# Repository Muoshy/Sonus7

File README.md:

# Sonus7
  Sonus7 is an analog seven-band spectrum bargraph with op amps. It consists of seven VU-meters, each being fed with a bandpass filter and peak detector circuit. 
  
  Each band has a spacing of 1.25 octaves. The bands are: 63 Hz, 160 Hz, 400 Hz, 1.25 kHz, 2.5 kHz, 6.25 kHz, 16 kHz. 
  
  The filters are second-order Multiple Feedback bandpass filters using TLC272 opamps. The VU-meters consist of a logaritmic comparator array, also using TLC272 opamps. The project is inspired by a reel of 2000 TLC272 bought cheaply at an auction.
  
# Features
- Fully analog (Except input stage)
- Seven frequency bands
- 10 levels per band
- 1.25 octave spacing
- 63 Hz to 16 kHz frequency range

# Filters
The filters were chosen to be Multiple Feedback filters since they allow independent adjustment of the gain $A_m$, filter quality $Q$ and mid frequency $f_m$. The transfer function and equations for calculating component values are taken from TI's design reference SLOD006B (16-31).

The gain and filter quality were set to $A_m = -10, \: Q = 6$ while capacitor values were chosen in the range of 33 to 0.33 nF to end up with reasonable resistor values. A MATLAB script is provided to calculate the exact resistor values and then round to nearest corresponding value from the E-24 series. The frequency responses are then simulated for the exact and rounded resistor values.

A final calculation is done to ensure the filter gains do not exceed the unity gain bandwidth (GBW) of the op amps. The actual amplification from the op amps is obtained from the noise gain. The noise gain is then multiplied with the corresponding mid frequency of each filter to obtain the (highest) GBW. This is also provided in the same MATLAB script. The calculation shows that all filters have a GBW below 2 MHz (TLC272), although the 16 kHz filter is close at 1.1 MHz. Thus, variations in temperature or other factors might limit the gain for 16 kHz filter and cause distortions.

The filtered signals are fed into peak detectors to obtain the audio level for each. The audio levels are then fed into the comparators which control the LEDs.

# Comparators
The comparators are built from open loop op amps. Reference voltage levels are generated from a logarithmic resistor divider (3 dB per step) and fed into the non-inverting inputs, essentially a logarithmic [Kelvin divider](https://en.wikipedia.org/wiki/Kelvin%E2%80%93Varley_divider). The inverting input is fed with the audio level. The op amp output can now function as a current sink for the LEDs. Any time the audio level exceeds the reference voltage level, the output is pulled low, allowing current flow for that level. Each op-amp drives one level, resulting in 70 op amps in total for the comparator stage.

# Construction

## PCBs
The Sonus7 consists of three boards (types).
### Input Stage
 The input stage consists of a custom board with an ESP32 and PCM5100. The ESP32 recieves the audio wirelessly through snapcast, using the port by [@CarlosDerSeher](https://github.com/CarlosDerSeher/snapclientThe). The audio data is then sent to the PCM5100 DAC over I2S. The input stage is connected to the next stage using a 4pin JST EH connector (VCC, GND, MONO, GND). The Kicad files for the input stage are available in /PCBs/ESP-input/.

### Filter and Comparator stage
The filter and comparator stage is the main board and contains all the filters and the comparator arrays. This board also contains the input power DC-jack (9V) along with a simple reverse input protection (PMOS) and thus powers the rest of the boards.

### LED bar
The final stage are the display boards. These are very simple boards with only LEDs, resistors and connectors on them. There is a small cutout on each level for the acrylic diffusers. There are seven of these boards, each one is connected to the main board using an ribbon cable (10p IDC) and a 2p JST cable (9V + GND).

## Mechanical

# Improvements
## Less cables
There is currently a 10p IDC for signal and a 2p JST for power. Combining power and signal into one connector (12p IDC) would tidy up the design.

## More stable supply voltage
Due to varying current draw (LEDs), the Drain-Source resistance of the PMOS causes to a varying voltage drop of 0-22 mV ( $R_{DS}$ = 32 mOhm, $I_{DS}$ = 0.7 A). This can cause issues for the op amps, which need a stable supply voltage. A simple fix could be adding a power regulator after the reverse input protection.

## GBW
The 16 kHz filter is quite close to the rated GBW of the TLC272. There is only a margin of $\frac{2}{1.1} \approx 1.8$ in gain before the limit. This can be solved by using cascaded filters which results in the individual gain of each op amp being smaller. Replacing the TLC272 with higher bandwidth op amps also works.

## Variable brightness
Currently the brightness of the LEDs are set by series resistors. Some brightness control using PWM or some other method could be good for the next version.

# Bill of Materials

# Contributors
**Daniel Quach** ([Muoshy](https://github.com/Muoshy))  
Main Contributor
- Filter design & Simulations
- PCB Design and assembly

**Johan Wheeler** ([johanwheeler](https://github.com/johanwheeler))
- Mechanical design
- Mechanical assembly

**Adam Anderson** ([adand00](https://github.com/adaand00))
- ESP input stage
- PCB Design and programming

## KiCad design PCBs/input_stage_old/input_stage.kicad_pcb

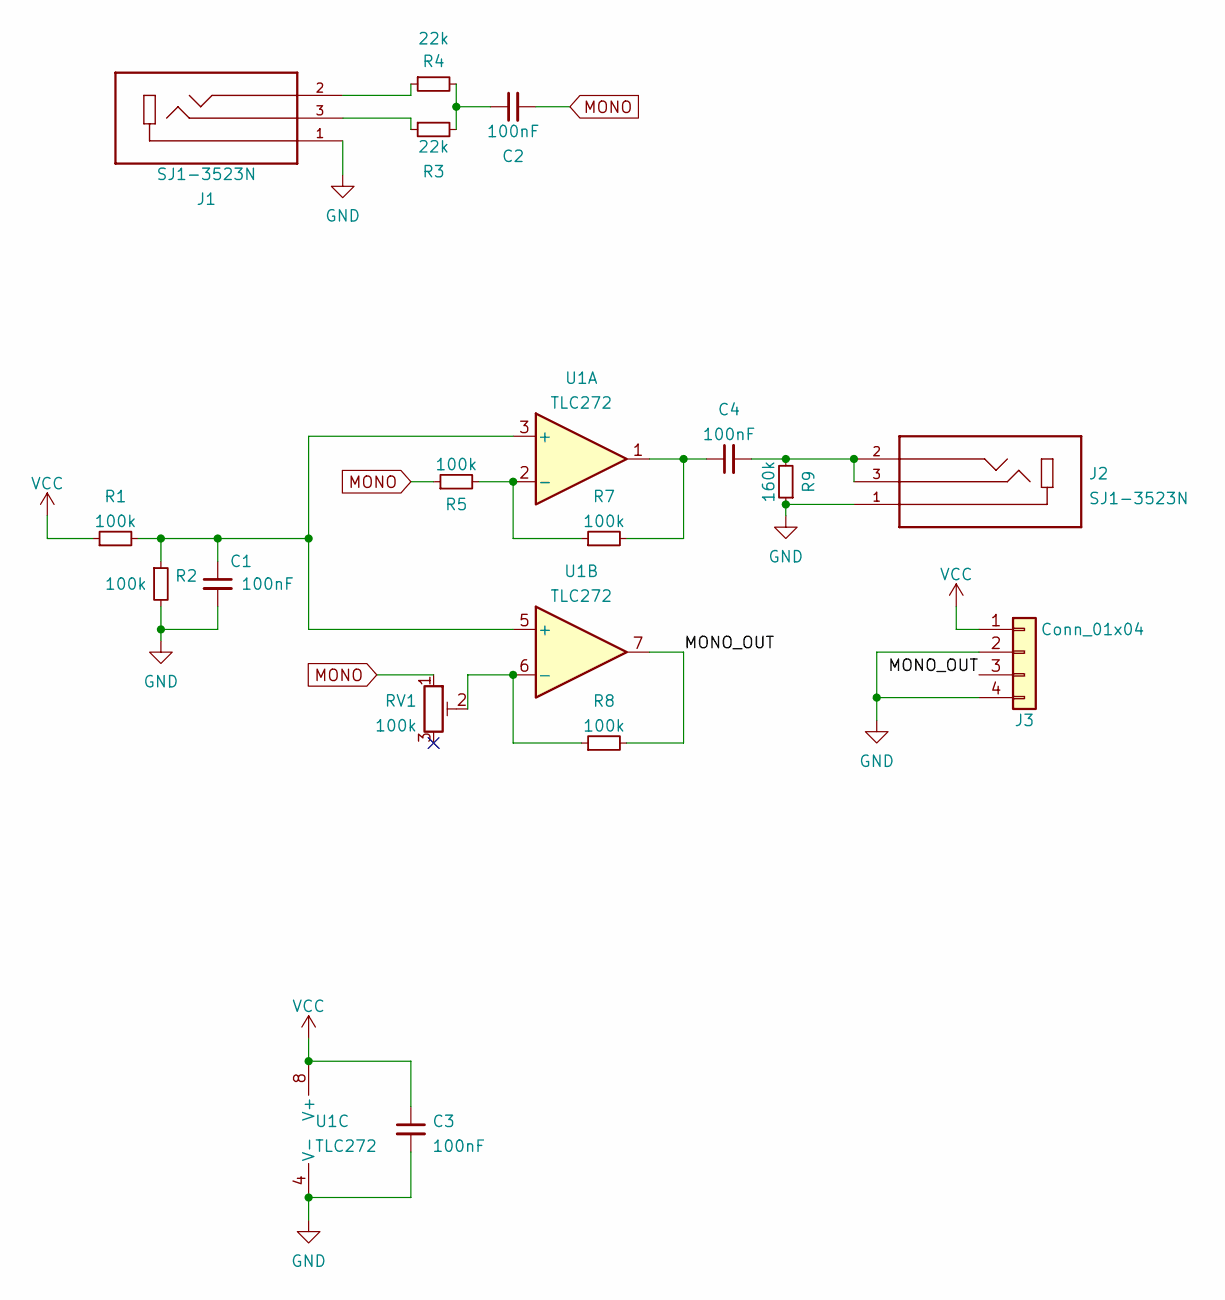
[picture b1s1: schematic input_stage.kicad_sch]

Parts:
C1, C2, C3, C4: 100nF; C_0603_1608Metric_Pad1.08x0.95mm_HandSolder
J1, J2: SJ1-3523N; CUI_SJ1-3523N; PARTREV 1.02
J3: Conn_01x04; JST_EH_S4B-EH_1x04_P2.50mm_Horizontal
R1, R2, R5, R7, R8: 100k; R_0603_1608Metric_Pad0.98x0.95mm_HandSolder
R3, R4: 22k; R_0603_1608Metric_Pad0.98x0.95mm_HandSolder
R9: 160k; R_0603_1608Metric_Pad0.98x0.95mm_HandSolder
RV1: 100k; Potentiometer_Bourns_TC33X_Vertical
U1: TLC272; SOIC-8_3.9x4.9mm_P1.27mm

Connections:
/MONO_OUT: J3.3, R8.2, U1.7
GND: C1.2, C3.2, J1.1, J2.1, J3.2, J3.4, R2.2, R9.1, U1.4 (V-)
MONO: C2.2, R5.1, RV1.1
unnamed: C1.1, R1.2, R2.1, U1.3 (+), U1.5 (+)
unnamed: C2.1, R3.2, R4.2
unnamed: J1.2, R4.1
unnamed: J1.3, R3.1
unnamed: C4.2, J2.2, J2.3, R9.2
unnamed: R5.2, R7.1, U1.2 (-)
unnamed: C4.1, R7.2, U1.1
unnamed: R8.1, RV1.2, U1.6 (-)
VCC: C3.1, J3.1, R1.1, U1.8 (V+)

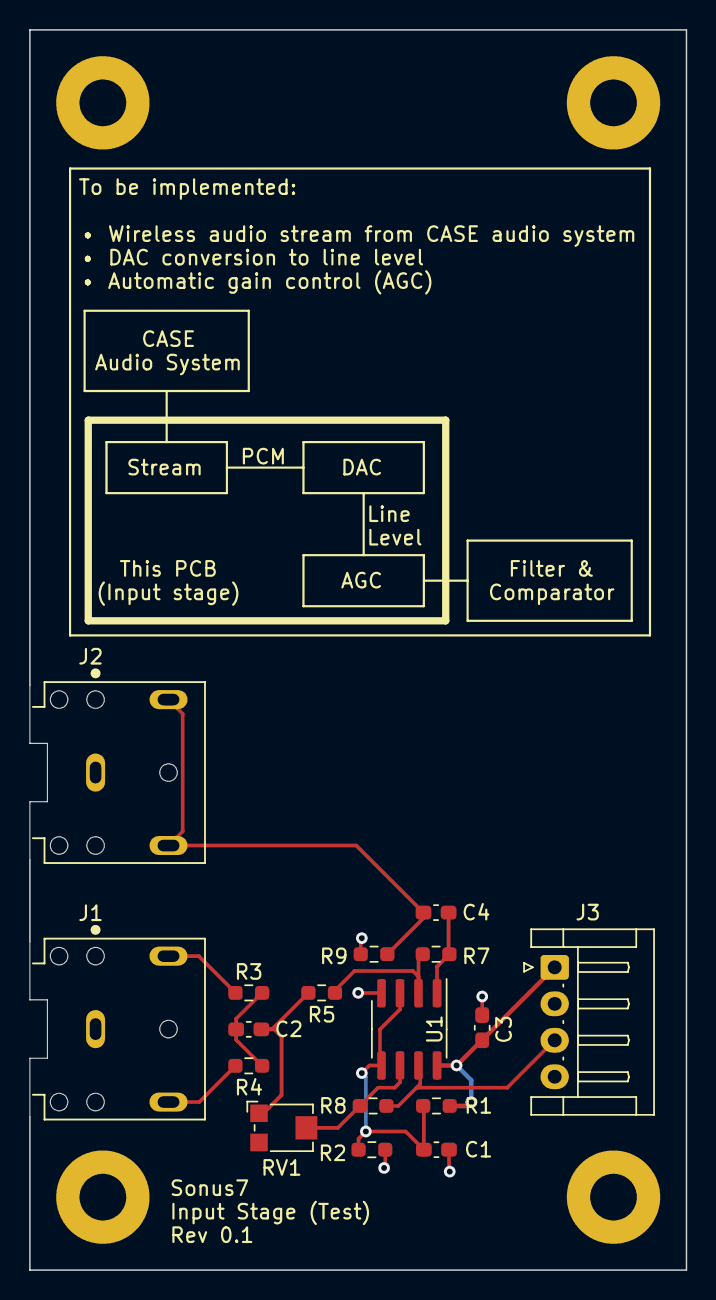
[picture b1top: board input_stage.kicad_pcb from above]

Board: 2 copper layers, 45.0 x 85.0 mm, 17 parts (0 on the bottom side), 12 nets.

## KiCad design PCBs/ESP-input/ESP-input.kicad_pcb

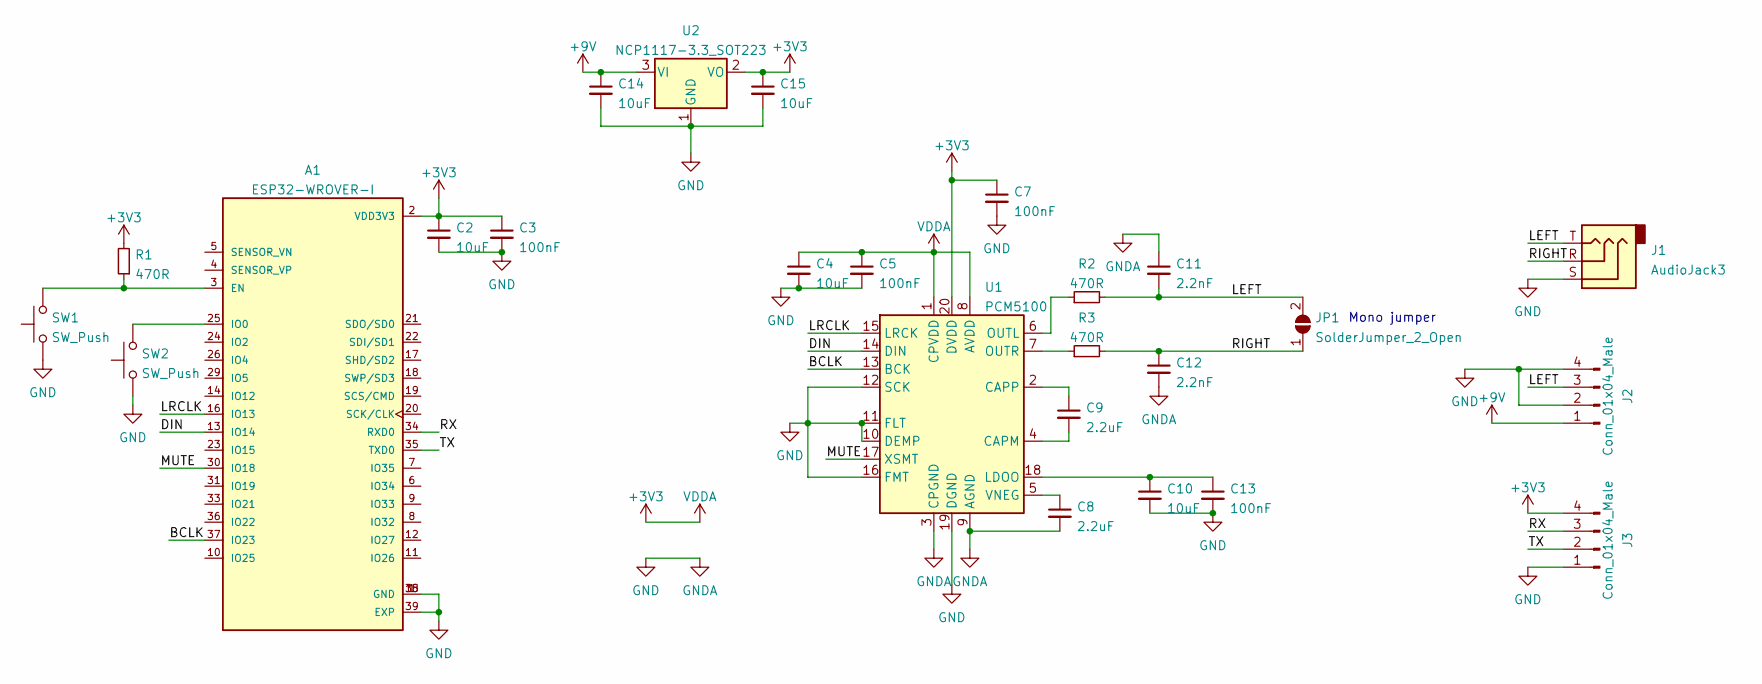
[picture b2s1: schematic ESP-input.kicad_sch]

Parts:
A1: ESP32-WROVER-I; DIGI-KEY_PART_NUMBER 1904-1008-1-ND
C2, C4, C10, C14, C15: 10uF; C_1206_3216Metric_Pad1.33x1.80mm_HandSolder
C3, C5, C7, C13: 100nF; C_0603_1608Metric_Pad1.08x0.95mm_HandSolder
C8, C9: 2.2uF; C_1206_3216Metric_Pad1.33x1.80mm_HandSolder
C11, C12: 2.2nF; C_0603_1608Metric_Pad1.08x0.95mm_HandSolder
J1: AudioJack3; Jack_3.5mm_CUI_SJ-3523-SMT_Horizontal
J2: Conn_01x04_Male; JST_EH_S4B-EH_1x04_P2.50mm_Horizontal
J3: Conn_01x04_Male; PinHeader_1x04_P2.54mm_Vertical
JP1: SolderJumper_2_Open; SolderJumper-2_P1.3mm_Open_TrianglePad1.0x1.5mm
R1, R2, R3: 470R; R_0603_1608Metric_Pad0.98x0.95mm_HandSolder
SW1, SW2: SW_Push; SW_Push_1P1T_NO_6x6mm_H9.5mm
U1: PCM5100; TSSOP-20_4.4x6.5mm_P0.65mm
U2: NCP1117-3.3_SOT223; SOT-223-3_TabPin2

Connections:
+3V3: A1.2 (VDD3V3), C2.1, C3.1, C4.1, C5.1, C7.1, C15.1, J3.4, R1.2, U1.1 (CPVDD), U1.8 (AVDD), U1.20 (DVDD), U2.2 (VO)
+9V: C14.1, J2.1, U2.3 (VI)
/BCLK: A1.37 (IO23), U1.13 (BCK)
/DIN: A1.13 (IO14), U1.14 (DIN)
/LEFT: C11.2, J1.T, J2.3, JP1.2 (B), R2.2
/LRCLK: A1.16 (IO13), U1.15 (LRCK)
/MUTE: A1.30 (IO18), U1.17 (XSMT)
/RIGHT: C12.1, J1.R, JP1.1 (A), R3.2
/RX: A1.34 (RXD0), J3.3
/TX: A1.35 (TXD0), J3.2
GND: A1.1 (GND), A1.15 (GND), A1.38 (GND), A1.39 (EXP), C2.2, C3.2, C4.2, C5.2, C7.2, C8.2, C10.2, C11.1, C12.2, C13.2, C14.2, C15.2, J1.S, J2.2, J2.4, J3.1, SW1.1, SW2.1, U1.3 (CPGND), U1.9 (AGND), U1.10 (DEMP), U1.11 (FLT), U1.12 (SCK), U1.16 (FMT), U1.19 (DGND), U2.1 (GND)
unnamed: A1.3 (EN), R1.1, SW1.2
unnamed: A1.25 (IO0), SW2.2
unnamed: C8.1, U1.5 (VNEG)
unnamed: C9.1, U1.2 (CAPP)
unnamed: C9.2, U1.4 (CAPM)
unnamed: C10.1, C13.1, U1.18 (LDOO)
unnamed: R2.1, U1.6 (OUTL)
unnamed: R3.1, U1.7 (OUTR)

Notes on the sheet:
Mono jumper

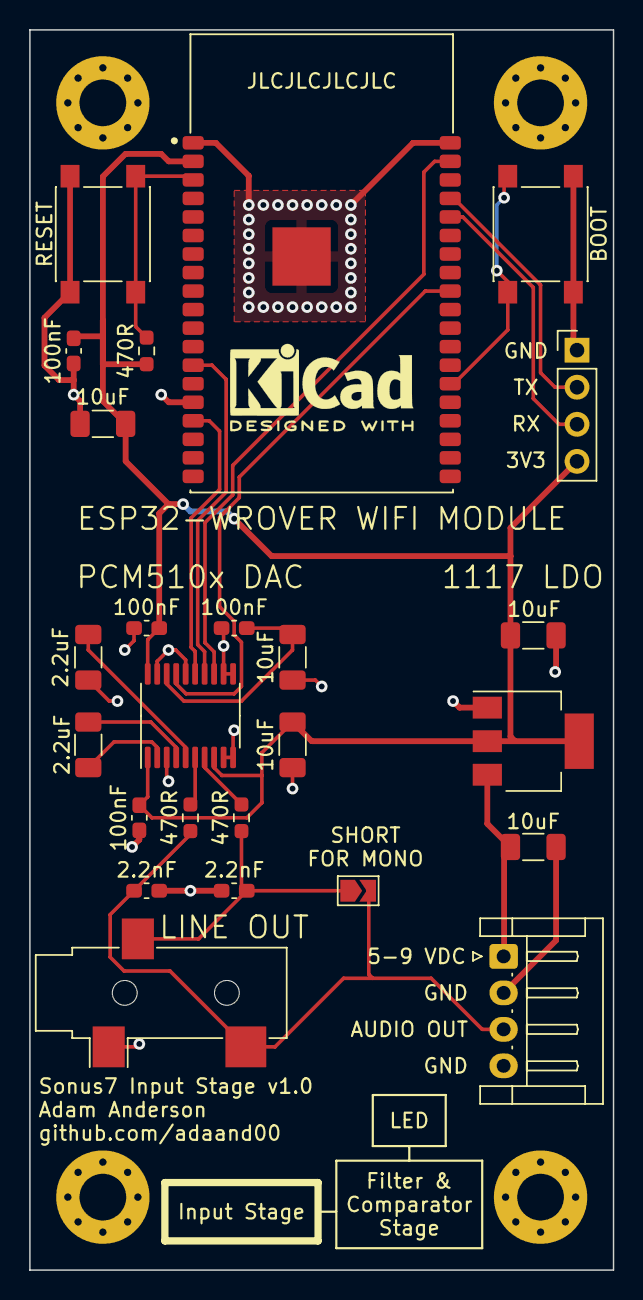
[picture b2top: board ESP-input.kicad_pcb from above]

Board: 2 copper layers, 40.0 x 85.0 mm, 25 parts (0 on the bottom side), 19 nets.

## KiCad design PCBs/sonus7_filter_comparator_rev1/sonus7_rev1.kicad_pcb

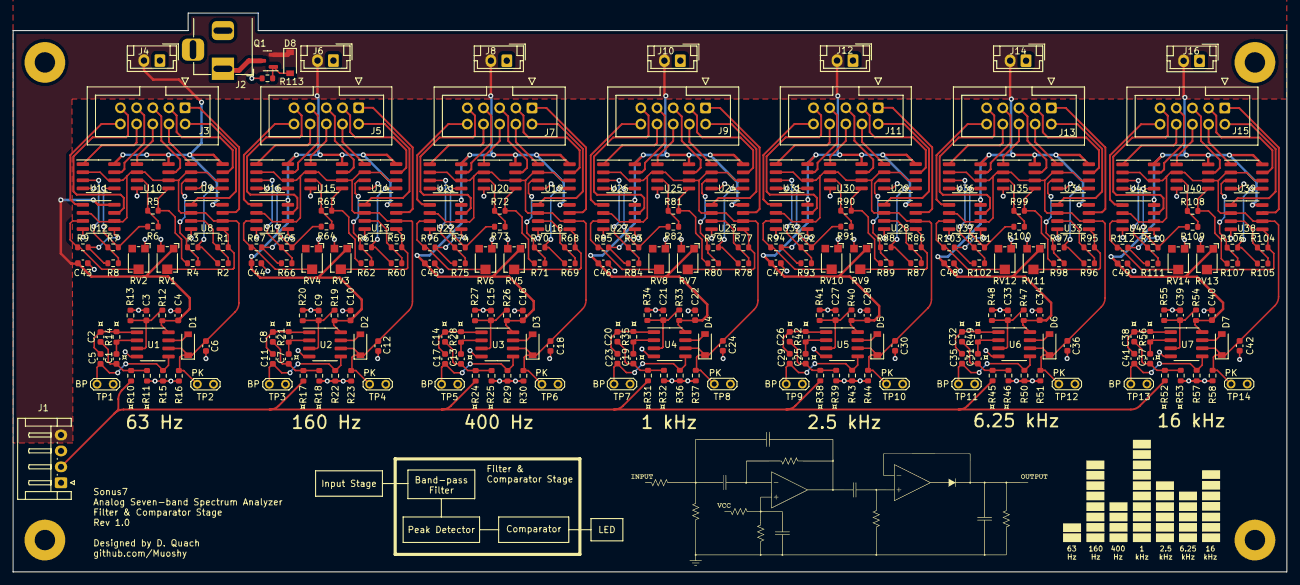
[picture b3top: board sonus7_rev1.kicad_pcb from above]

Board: 2 copper layers, 200.0 x 87.8 mm, 257 parts (0 on the bottom side), 194 nets.

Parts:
C1, C2, C7, C8, C13, C14, C19, C20, C25, C26, C31, C32, C37, C38: C; C_0603_1608Metric
C3, C4, C5, C9, C10, C11, C15, C16, C17, C21, C22, C23, C27, C28, C29, C33, C34, C35, C39, C40, C41, C43, C44, C45, C46, C47, C48, C49: 100n; C_0603_1608Metric
C6, C12, C18, C24, C30, C36, C42: 220n; C_0603_1608Metric
D1, D2, D3, D4, D5, D6, D7: 1N4148; D_SOD-123
D8: 8.2V; D_SOD-123
J1: Conn_01x04; JST_EH_S4B-EH_1x04_P2.50mm_Horizontal
J2: DC-Jack; BarrelJack_Horizontal
J3, J5, J7, J9, J11, J13, J15: Conn_02x05_Counter_Clockwise; IDC-Header_2x05_P2.54mm_Vertical
J4, J6, J8, J10, J12, J14, J16: Conn_01x02; JST_EH_B2B-EH-A_1x02_P2.50mm_Vertical
Q1: IRLML6402; SOT-23
R1, R59, R68, R77, R86, R95, R104: 13k; R_0603_1608Metric
R2, R60, R69, R78, R87, R96, R105: 9.1k; R_0603_1608Metric
R3, R61, R70, R79, R88, R97, R106: 6.2k; R_0603_1608Metric
R4, R62, R71, R80, R89, R98, R107: 4.3k; R_0603_1608Metric
R5, R63, R72, R81, R90, R99, R108: 3k; R_0603_1608Metric
R6, R64, R73, R82, R91, R100, R109: 2.2k; R_0603_1608Metric
R7, R65, R74, R83, R92, R101, R110: 1.6k; R_0603_1608Metric
R8, R66, R75, R84, R93, R102, R111: 1.1k; R_0603_1608Metric
R9, R67, R76, R85, R94, R103, R112: 750k; R_0603_1608Metric
R10, R17, R24, R31, R38, R45, R52: R1; R_0603_1608Metric
R11, R18, R25, R32, R39, R46, R53: R3; R_0603_1608Metric
R12, R13, R19, R20, R26, R27, R33, R34, R40, R41, R47, R48, R54, R55: 100k; R_0603_1608Metric
R14, R21, R28, R35, R42, R49, R56: R2; R_0603_1608Metric
R15, R22, R29, R36, R43, R50, R57: 160k; R_0603_1608Metric
R16, R23, R30, R37, R44, R51, R58: 220k; R_0603_1608Metric
R113: 100R; R_0603_1608Metric
RV1, RV3, RV5, RV7, RV9, RV11, RV13: R_U; Potentiometer_Bourns_TC33X_Vertical
RV2, RV4, RV6, RV8, RV10, RV12, RV14: R_L; Potentiometer_Bourns_TC33X_Vertical
TP1, TP3, TP5, TP7, TP9, TP11, TP13: TP_BP; TestPoint_2Pads_Pitch2.54mm_Drill0.8mm
TP2, TP4, TP6, TP8, TP10, TP12, TP14: TP_PEAK; TestPoint_2Pads_Pitch2.54mm_Drill0.8mm
U1, U2, U3, U4, U5, U6, U7, U8, U9, U10, U11, U12, U13, U14, U15, U16, U17, U18, U19, U20, U21, U22, U23, U24, U25, U26, U27, U28, U29, U30, U31, U32, U33, U34, U35, U36, U37, U38, U39, U40, U41, U42: TLC272; SOIC-8_3.9x4.9mm_P1.27mm

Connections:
/Filter 1 kHz/BP_OUT: C23.2, R36.2, TP7.1, U4.5 (+)
/Filter 1 kHz/OUTPUT: C24.2, D4.1 (K), R37.1, TP8.1, U4.6 (-), U23.2 (-), U23.6 (-), U24.2 (-), U24.6 (-), U25.2 (-), U25.6 (-), U26.2 (-), U26.6 (-), U27.2 (-), U27.6 (-)
/Filter 2.5 kHz/BP_OUT: C29.2, R43.2, TP9.1, U5.5 (+)
/Filter 2.5 kHz/OUTPUT: C30.2, D5.1 (K), R44.1, TP10.1, U5.6 (-), U28.2 (-), U28.6 (-), U29.2 (-), U29.6 (-), U30.2 (-), U30.6 (-), U31.2 (-), U31.6 (-), U32.2 (-), U32.6 (-)
/Filter 6.25 kHz/BP_OUT: C35.2, R50.2, TP11.1, U6.5 (+)
/Filter 6.25 kHz/OUTPUT: C36.2, D6.1 (K), R51.1, TP12.1, U6.6 (-), U33.2 (-), U33.6 (-), U34.2 (-), U34.6 (-), U35.2 (-), U35.6 (-), U36.2 (-), U36.6 (-), U37.2 (-), U37.6 (-)
/Filter 16 kHz/BP_OUT: C41.2, R57.2, TP13.1, U7.5 (+)
/Filter 16 kHz/OUTPUT: C42.2, D7.1 (K), R58.1, TP14.1, U7.6 (-), U38.2 (-), U38.6 (-), U39.2 (-), U39.6 (-), U40.2 (-), U40.6 (-), U41.2 (-), U41.6 (-), U42.2 (-), U42.6 (-)
/Filter 63 Hz/BP_OUT: C5.2, R15.2, TP1.1, U1.5 (+)
/Filter 63 Hz/OUTPUT: C6.2, D1.1 (K), R16.1, TP2.1, U1.6 (-), U8.2 (-), U8.6 (-), U9.2 (-), U9.6 (-), U10.2 (-), U10.6 (-), U11.2 (-), U11.6 (-), U12.2 (-), U12.6 (-)
/Filter 160 Hz/BP_OUT: C11.2, R22.2, TP3.1, U2.5 (+)
/Filter 160 Hz/OUTPUT: C12.2, D2.1 (K), R23.1, TP4.1, U2.6 (-), U13.2 (-), U13.6 (-), U14.2 (-), U14.6 (-), U15.2 (-), U15.6 (-), U16.2 (-), U16.6 (-), U17.2 (-), U17.6 (-)
/Filter 400 Hz/BP_OUT: C17.2, R29.2, TP5.1, U3.5 (+)
/Filter 400 Hz/OUTPUT: C18.2, D3.1 (K), R30.1, TP6.1, U3.6 (-), U18.2 (-), U18.6 (-), U19.2 (-), U19.6 (-), U20.2 (-), U20.6 (-), U21.2 (-), U21.6 (-), U22.2 (-), U22.6 (-)
/Log Comp 1 kHz/LV1: R85.1, RV8.2, U27.3 (+)
/Log Comp 1 kHz/LV2: R84.1, R85.2, U27.5 (+)
/Log Comp 1 kHz/LV3: R83.1, R84.2, U26.3 (+)
/Log Comp 1 kHz/LV4: R82.1, R83.2, U26.5 (+)
/Log Comp 1 kHz/LV5: R81.1, R82.2, U25.3 (+)
/Log Comp 1 kHz/LV6: R80.1, R81.2, U25.5 (+)
/Log Comp 1 kHz/LV7: R79.1, R80.2, U24.3 (+)
/Log Comp 1 kHz/LV8: R78.1, R79.2, U24.5 (+)
/Log Comp 1 kHz/LV9: R77.1, R78.2, U23.3 (+)
/Log Comp 1 kHz/LV10: R77.2, RV7.2, U23.5 (+)
/Log Comp 2.5 kHz/LV1: R94.1, RV10.2, U32.3 (+)
/Log Comp 2.5 kHz/LV2: R93.1, R94.2, U32.5 (+)
/Log Comp 2.5 kHz/LV3: R92.1, R93.2, U31.3 (+)
/Log Comp 2.5 kHz/LV4: R91.1, R92.2, U31.5 (+)
/Log Comp 2.5 kHz/LV5: R90.1, R91.2, U30.3 (+)
/Log Comp 2.5 kHz/LV6: R89.1, R90.2, U30.5 (+)
/Log Comp 2.5 kHz/LV7: R88.1, R89.2, U29.3 (+)
/Log Comp 2.5 kHz/LV8: R87.1, R88.2, U29.5 (+)
/Log Comp 2.5 kHz/LV9: R86.1, R87.2, U28.3 (+)
/Log Comp 2.5 kHz/LV10: R86.2, RV9.2, U28.5 (+)
/Log Comp 6.25 kHz/LV1: R103.1, RV12.2, U37.3 (+)
/Log Comp 6.25 kHz/LV2: R102.1, R103.2, U37.5 (+)
/Log Comp 6.25 kHz/LV3: R101.1, R102.2, U36.3 (+)
/Log Comp 6.25 kHz/LV4: R100.1, R101.2, U36.5 (+)
/Log Comp 6.25 kHz/LV5: R99.1, R100.2, U35.3 (+)
/Log Comp 6.25 kHz/LV6: R98.1, R99.2, U35.5 (+)
/Log Comp 6.25 kHz/LV7: R97.1, R98.2, U34.3 (+)
/Log Comp 6.25 kHz/LV8: R96.1, R97.2, U34.5 (+)
/Log Comp 6.25 kHz/LV9: R95.1, R96.2, U33.3 (+)
/Log Comp 6.25 kHz/LV10: R95.2, RV11.2, U33.5 (+)
/Log Comp 16 kHz/LV1: R112.1, RV14.2, U42.3 (+)
/Log Comp 16 kHz/LV2: R111.1, R112.2, U42.5 (+)
/Log Comp 16 kHz/LV3: R110.1, R111.2, U41.3 (+)
/Log Comp 16 kHz/LV4: R109.1, R110.2, U41.5 (+)
/Log Comp 16 kHz/LV5: R108.1, R109.2, U40.3 (+)
/Log Comp 16 kHz/LV6: R107.1, R108.2, U40.5 (+)
/Log Comp 16 kHz/LV7: R106.1, R107.2, U39.3 (+)
/Log Comp 16 kHz/LV8: R105.1, R106.2, U39.5 (+)
/Log Comp 16 kHz/LV9: R104.1, R105.2, U38.3 (+)
/Log Comp 16 kHz/LV10: R104.2, RV13.2, U38.5 (+)
/Log Comp 63 Hz/LV1: R9.1, RV2.2, U12.3 (+)
/Log Comp 63 Hz/LV2: R8.1, R9.2, U12.5 (+)
/Log Comp 63 Hz/LV3: R7.1, R8.2, U11.3 (+)
/Log Comp 63 Hz/LV4: R6.1, R7.2, U11.5 (+)
/Log Comp 63 Hz/LV5: R5.1, R6.2, U10.3 (+)
/Log Comp 63 Hz/LV6: R4.1, R5.2, U10.5 (+)
/Log Comp 63 Hz/LV7: R3.1, R4.2, U9.3 (+)
/Log Comp 63 Hz/LV8: R2.1, R3.2, U9.5 (+)
/Log Comp 63 Hz/LV9: R1.1, R2.2, U8.3 (+)
/Log Comp 63 Hz/LV10: R1.2, RV1.2, U8.5 (+)
/Log Comp 160 Hz/LV1: R67.1, RV4.2, U17.3 (+)
/Log Comp 160 Hz/LV2: R66.1, R67.2, U17.5 (+)
/Log Comp 160 Hz/LV3: R65.1, R66.2, U16.3 (+)
/Log Comp 160 Hz/LV4: R64.1, R65.2, U16.5 (+)
/Log Comp 160 Hz/LV5: R63.1, R64.2, U15.3 (+)
/Log Comp 160 Hz/LV6: R62.1, R63.2, U15.5 (+)
/Log Comp 160 Hz/LV7: R61.1, R62.2, U14.3 (+)
/Log Comp 160 Hz/LV8: R60.1, R61.2, U14.5 (+)
/Log Comp 160 Hz/LV9: R59.1, R60.2, U13.3 (+)
/Log Comp 160 Hz/LV10: R59.2, RV3.2, U13.5 (+)
/Log Comp 400 Hz/LV1: R76.1, RV6.2, U22.3 (+)
/Log Comp 400 Hz/LV2: R75.1, R76.2, U22.5 (+)
/Log Comp 400 Hz/LV3: R74.1, R75.2, U21.3 (+)
/Log Comp 400 Hz/LV4: R73.1, R74.2, U21.5 (+)
/Log Comp 400 Hz/LV5: R72.1, R73.2, U20.3 (+)
/Log Comp 400 Hz/LV6: R71.1, R72.2, U20.5 (+)
/Log Comp 400 Hz/LV7: R70.1, R71.2, U19.3 (+)
/Log Comp 400 Hz/LV8: R69.1, R70.2, U19.5 (+)
/Log Comp 400 Hz/LV9: R68.1, R69.2, U18.3 (+)
/Log Comp 400 Hz/LV10: R68.2, RV5.2, U18.5 (+)
/PWR_IN: J2.1, Q1.3 (D)
GND: C3.2, C4.2, C6.1, C9.2, C10.2, C12.1, C15.2, C16.2, C18.1, C21.2, C22.2, C24.1, C27.2, C28.2, C30.1, C33.2, C34.2, C36.1, C39.2, C40.2, C42.1, C43.2, C44.2, C45.2, C46.2, C47.2, C48.2, C49.2, J1.1, J1.3, J2.2, J2.3, J4.1, J6.1, J8.1, J10.1, J12.1, J14.1, J16.1, R11.2, R13.2, R15.1, R16.2, R18.2, R20.2, R22.1, R23.2, R25.2, R27.2, R29.1, R30.2, R32.2, R34.2, R36.1, R37.2, R39.2, R41.2, R43.1, R44.2, R46.2, R48.2, R50.1, R51.2, R53.2, R55.2, R57.1, R58.2, R113.2, RV1.3, RV2.1, RV3.3, RV4.1, RV5.3, RV6.1, RV7.3, RV8.1, RV9.3, RV10.1, RV11.3, RV12.1, RV13.3, RV14.1, TP1.2, TP2.2, TP3.2, TP4.2, TP5.2, TP6.2, TP7.2, TP8.2, TP9.2, TP10.2, TP11.2, TP12.2, TP13.2, TP14.2, U1.4 (V-), U2.4 (V-), U3.4 (V-), U4.4 (V-), U5.4 (V-), U6.4 (V-), U7.4 (V-), U8.4 (V-), U9.4 (V-), U10.4 (V-), U11.4 (V-), U12.4 (V-), U13.4 (V-), U14.4 (V-), U15.4 (V-), U16.4 (V-), U17.4 (V-), U18.4 (V-), U19.4 (V-), U20.4 (V-), U21.4 (V-), U22.4 (V-), U23.4 (V-), U24.4 (V-), U25.4 (V-), U26.4 (V-), U27.4 (V-), U28.4 (V-), U29.4 (V-), U30.4 (V-), U31.4 (V-), U32.4 (V-), U33.4 (V-), U34.4 (V-), U35.4 (V-), U36.4 (V-), U37.4 (V-), U38.4 (V-), U39.4 (V-), U40.4 (V-), U41.4 (V-), U42.4 (V-)
MONO: J1.2, R10.1, R17.1, R24.1, R31.1, R38.1, R45.1, R52.1
unnamed: C1.1, C2.1, R10.2, R11.1
unnamed: C1.2, R14.1, U1.2 (-)
unnamed: C2.2, C5.1, R14.2, U1.1
unnamed: C3.1, R12.2, R13.1, U1.3 (+)
unnamed: C7.1, C8.1, R17.2, R18.1
unnamed: C7.2, R21.1, U2.2 (-)
unnamed: C9.1, R19.2, R20.1, U2.3 (+)
unnamed: C8.2, C11.1, R21.2, U2.1
unnamed: C13.1, C14.1, R24.2, R25.1
unnamed: C13.2, R28.1, U3.2 (-)
unnamed: C14.2, C17.1, R28.2, U3.1
unnamed: C15.1, R26.2, R27.1, U3.3 (+)
unnamed: C19.1, C20.1, R31.2, R32.1
unnamed: C19.2, R35.1, U4.2 (-)
unnamed: C20.2, C23.1, R35.2, U4.1
unnamed: C21.1, R33.2, R34.1, U4.3 (+)
unnamed: C25.1, C26.1, R38.2, R39.1
unnamed: C25.2, R42.1, U5.2 (-)
unnamed: C26.2, C29.1, R42.2, U5.1
unnamed: C27.1, R40.2, R41.1, U5.3 (+)
unnamed: C31.1, C32.1, R45.2, R46.1
unnamed: C31.2, R49.1, U6.2 (-)
unnamed: C32.2, C35.1, R49.2, U6.1
unnamed: C33.1, R47.2, R48.1, U6.3 (+)
unnamed: C37.1, C38.1, R52.2, R53.1
unnamed: C37.2, R56.1, U7.2 (-)
unnamed: C38.2, C41.1, R56.2, U7.1
unnamed: C39.1, R54.2, R55.1, U7.3 (+)
unnamed: D1.2 (A), U1.7
unnamed: D2.2 (A), U2.7
unnamed: D3.2 (A), U3.7
unnamed: D4.2 (A), U4.7
unnamed: D5.2 (A), U5.7
unnamed: D6.2 (A), U6.7
unnamed: D7.2 (A), U7.7
unnamed: D8.2 (A), Q1.1 (G), R113.1
unnamed: J3.1, U8.7
unnamed: J3.2, U8.1
unnamed: J3.3, U9.7
unnamed: J3.4, U9.1
unnamed: J3.5, U10.7
unnamed: J3.6, U10.1
unnamed: J3.7, U11.7
unnamed: J3.8, U11.1
unnamed: J3.9, U12.7
unnamed: J3.10, U12.1
unnamed: J5.1, U13.7
unnamed: J5.2, U13.1
unnamed: J5.3, U14.7
unnamed: J5.4, U14.1
unnamed: J5.5, U15.7
unnamed: J5.6, U15.1
unnamed: J5.7, U16.7
unnamed: J5.8, U16.1
unnamed: J5.9, U17.7
unnamed: J5.10, U17.1
unnamed: J7.1, U18.7
unnamed: J7.2, U18.1
unnamed: J7.3, U19.7
unnamed: J7.4, U19.1
unnamed: J7.5, U20.7
unnamed: J7.6, U20.1
unnamed: J7.7, U21.7
unnamed: J7.8, U21.1
unnamed: J7.9, U22.7
unnamed: J7.10, U22.1
unnamed: J9.1, U23.7
unnamed: J9.2, U23.1
unnamed: J9.3, U24.7
unnamed: J9.4, U24.1
unnamed: J9.5, U25.7
unnamed: J9.6, U25.1
unnamed: J9.7, U26.7
unnamed: J9.8, U26.1
unnamed: J9.9, U27.7
unnamed: J9.10, U27.1
unnamed: J11.1, U28.7
unnamed: J11.2, U28.1
unnamed: J11.3, U29.7
unnamed: J11.4, U29.1
unnamed: J11.5, U30.7
unnamed: J11.6, U30.1
unnamed: J11.7, U31.7
unnamed: J11.8, U31.1
unnamed: J11.9, U32.7
unnamed: J11.10, U32.1
unnamed: J13.1, U33.7
unnamed: J13.2, U33.1
unnamed: J13.3, U34.7
unnamed: J13.4, U34.1
unnamed: J13.5, U35.7
unnamed: J13.6, U35.1
unnamed: J13.7, U36.7
unnamed: J13.8, U36.1
unnamed: J13.9, U37.7
unnamed: J13.10, U37.1
unnamed: J15.1, U38.7
unnamed: J15.2, U38.1
unnamed: J15.3, U39.7
unnamed: J15.4, U39.1
unnamed: J15.5, U40.7
unnamed: J15.6, U40.1
unnamed: J15.7, U41.7
unnamed: J15.8, U41.1
unnamed: J15.9, U42.7
unnamed: J15.10, U42.1
VCC: C4.1, C10.1, C16.1, C22.1, C28.1, C34.1, C40.1, C43.1, C44.1, C45.1, C46.1, C47.1, C48.1, C49.1, D8.1 (K), J1.4, J4.2, J6.2, J8.2, J10.2, J12.2, J14.2, J16.2, Q1.2 (S), R12.1, R19.1, R26.1, R33.1, R40.1, R47.1, R54.1, RV1.1, RV3.1, RV5.1, RV7.1, RV9.1, RV11.1, RV13.1, U1.8 (V+), U2.8 (V+), U3.8 (V+), U4.8 (V+), U5.8 (V+), U6.8 (V+), U7.8 (V+), U8.8 (V+), U9.8 (V+), U10.8 (V+), U11.8 (V+), U12.8 (V+), U13.8 (V+), U14.8 (V+), U15.8 (V+), U16.8 (V+), U17.8 (V+), U18.8 (V+), U19.8 (V+), U20.8 (V+), U21.8 (V+), U22.8 (V+), U23.8 (V+), U24.8 (V+), U25.8 (V+), U26.8 (V+), U27.8 (V+), U28.8 (V+), U29.8 (V+), U30.8 (V+), U31.8 (V+), U32.8 (V+), U33.8 (V+), U34.8 (V+), U35.8 (V+), U36.8 (V+), U37.8 (V+), U38.8 (V+), U39.8 (V+), U40.8 (V+), U41.8 (V+), U42.8 (V+)

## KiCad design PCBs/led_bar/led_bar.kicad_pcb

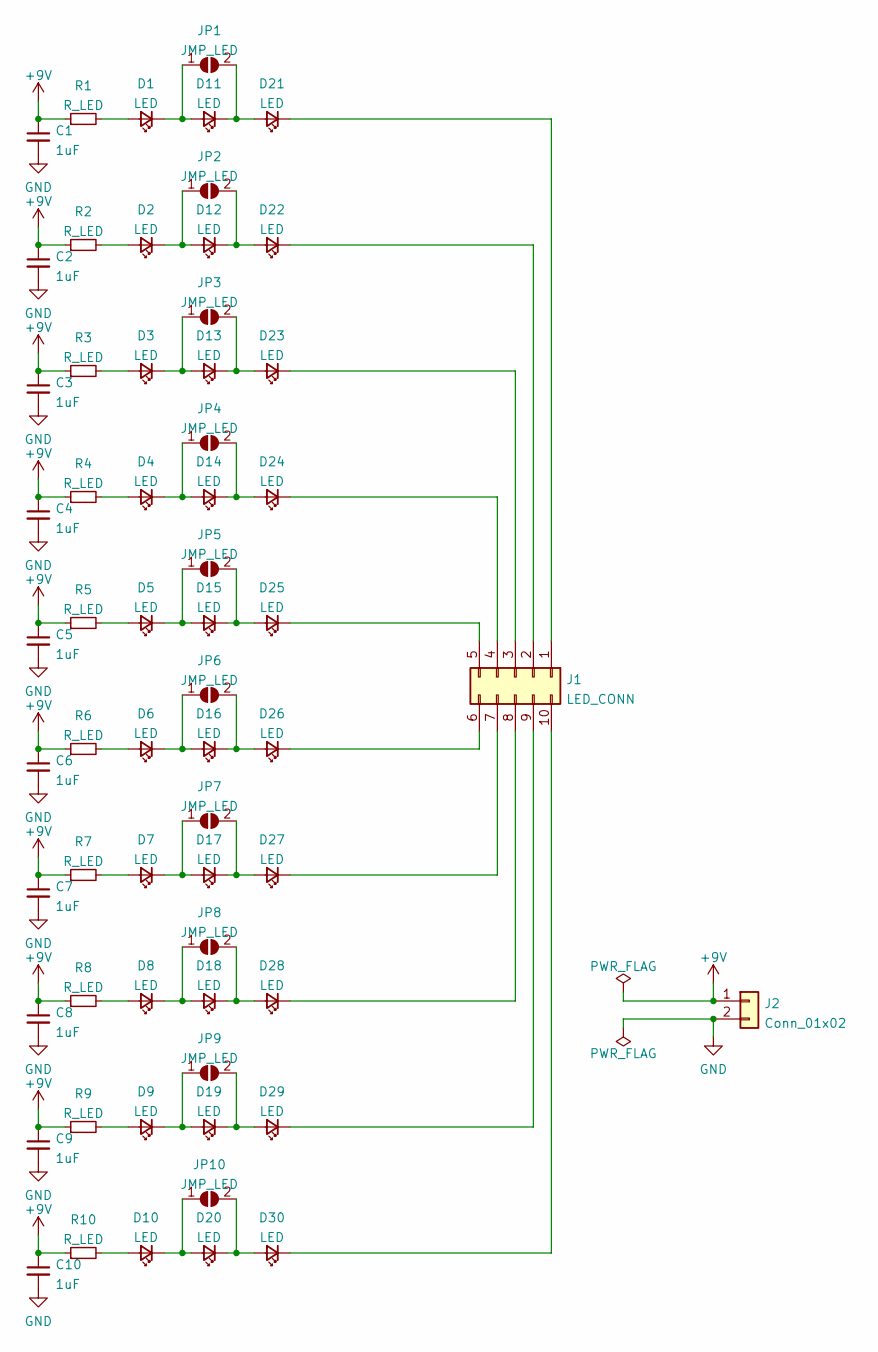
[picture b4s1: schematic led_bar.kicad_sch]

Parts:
C1, C2, C3, C4, C5, C6, C7, C8, C9, C10: 1uF; C_0805_2012Metric_Pad1.18x1.45mm_HandSolder
D1, D2, D3, D4, D5, D6, D7, D8, D9, D10, D11, D12, D13, D14, D15, D16, D17, D18, D19, D20, D21, D22, D23, D24, D25, D26, D27, D28, D29, D30: LED; LED_5mm_DUAL
J1: LED_CONN; IDC-Header_2x05_P2.54mm_Vertical
J2: Conn_01x02; JST_EH_B2B-EH-A_1x02_P2.50mm_Vertical
JP1, JP2, JP3, JP4, JP5, JP6, JP7, JP8, JP9, JP10: JMP_LED; SolderJumper-2_P1.3mm_Open_TrianglePad1.0x1.5mm
R1, R2, R3, R4, R5, R6, R7, R8, R9, R10: R_LED; R_0805_2012Metric_Pad1.20x1.40mm_HandSolder

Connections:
+9V: C1.1, C2.1, C3.1, C4.1, C5.1, C6.1, C7.1, C8.1, C9.1, C10.1, J2.1, R1.1, R2.1, R3.1, R4.1, R5.1, R6.1, R7.1, R8.1, R9.1, R10.1
GND: C1.2, C2.2, C3.2, C4.2, C5.2, C6.2, C7.2, C8.2, C9.2, C10.2, J2.2
unnamed: D1.1 (K), D11.2 (A), JP1.1 (A)
unnamed: D1.2 (A), R1.2
unnamed: D2.2 (A), R2.2
unnamed: D3.2 (A), R3.2
unnamed: D4.2 (A), R4.2
unnamed: D5.2 (A), R5.2
unnamed: D6.2 (A), R6.2
unnamed: D7.2 (A), R7.2
unnamed: D8.2 (A), R8.2
unnamed: D9.2 (A), R9.2
unnamed: D10.1 (K), D20.2 (A), JP10.1 (A)
unnamed: D10.2 (A), R10.2
unnamed: D11.1 (K), D21.2 (A), JP1.2 (B)
unnamed: D12.1 (K), D22.2 (A), JP2.2 (B)
unnamed: D2.1 (K), D12.2 (A), JP2.1 (A)
unnamed: D13.1 (K), D23.2 (A), JP3.2 (B)
unnamed: D3.1 (K), D13.2 (A), JP3.1 (A)
unnamed: D14.1 (K), D24.2 (A), JP4.2 (B)
unnamed: D4.1 (K), D14.2 (A), JP4.1 (A)
unnamed: D15.1 (K), D25.2 (A), JP5.2 (B)
unnamed: D5.1 (K), D15.2 (A), JP5.1 (A)
unnamed: D16.1 (K), D26.2 (A), JP6.2 (B)
unnamed: D6.1 (K), D16.2 (A), JP6.1 (A)
unnamed: D17.1 (K), D27.2 (A), JP7.2 (B)
unnamed: D7.1 (K), D17.2 (A), JP7.1 (A)
unnamed: D18.1 (K), D28.2 (A), JP8.2 (B)
unnamed: D8.1 (K), D18.2 (A), JP8.1 (A)
unnamed: D19.1 (K), D29.2 (A), JP9.2 (B)
unnamed: D9.1 (K), D19.2 (A), JP9.1 (A)
unnamed: D20.1 (K), D30.2 (A), JP10.2 (B)
unnamed: D21.1 (K), J1.1
unnamed: D22.1 (K), J1.2
unnamed: D23.1 (K), J1.3
unnamed: D24.1 (K), J1.4
unnamed: D25.1 (K), J1.5
unnamed: D26.1 (K), J1.6
unnamed: D27.1 (K), J1.7
unnamed: D28.1 (K), J1.8
unnamed: D29.1 (K), J1.9
unnamed: D30.1 (K), J1.10

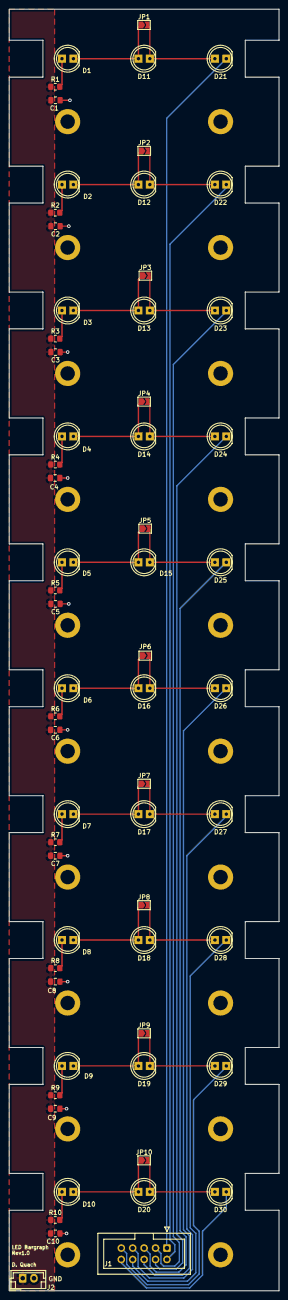
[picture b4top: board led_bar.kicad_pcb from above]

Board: 2 copper layers, 60.0 x 285.0 mm, 62 parts (0 on the bottom side), 42 nets.

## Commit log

2022-09-23 Upload MATLAB script MFB_BP_SIM.m
    MATLAB script for calculating filter parameters and simulations
2022-09-25 add round63 library
2022-09-25 add img of plots
2022-10-10 Added images
2022-10-10 Add LED bar files
2022-10-10 Add Filter & comparator files
2022-10-20 ESP-input v1.0
2022-10-20 Add Zipped GRBs
2022-11-01 add filter img
2022-11-21 Add info bout input stage
2022-11-21 Not fully analog any more :/
2022-12-21 Added files for old input stage
2023-08-17 Added some cad files
2023-10-19 Added clip of it running
